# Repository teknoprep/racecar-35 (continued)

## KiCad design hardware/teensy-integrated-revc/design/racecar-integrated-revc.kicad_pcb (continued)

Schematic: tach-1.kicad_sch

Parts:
C19: 1n; C_0805_2012Metric
C20, C21: 100n; C_0805_2012Metric
D4: LM4040 2.5; SOT-23
D5: PMEG2010ER; Nexperia_CFP3_SOD-123W
J3: TACH INPUT; TerminalBlock_Phoenix_MKDS-1,5-2-5.08_1x02_P5.08mm_Horizont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
Q1: MMBT3904; SOT-23
R4: 180k 1%; R_0805_2012Metric
R5: 22k 1%; R_0805_2012Metric
R6: 240k 1%; R_0805_2012Metric
R7, R10: 10k 1%; R_0805_2012Metric
R8: 2.2M 1%; R_0805_2012Metric
R9: 4.7k 1%; R_0805_2012Metric
R11: 100k 1%; R_0805_2012Metric
U11: LM2903B; SOIC-8_3.9x4.9mm_P1.27mm

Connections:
+5V_MAIN: C21.1, R6.1, R9.1, U11.8 (VCC); also elsewhere on the board
GND: C19.2, C20.2, C21.2, D4.2 (A), D4.3 (A/NC), D5.2 (A), J3.2 (RETURN), Q1.2 (E), R5.2, R7.2, R11.2, U11.4 (GND), U11.5 (IN2+); also elsewhere on the board
TACH_BASE: Q1.1 (B), R10.2, R11.1
TACH_CMP: R8.1, R9.2, R10.1, U11.1 (OUT1)
TACH_IN: J3.1 (SIGNAL), R4.1
TACH_LED_K: Q1.3 (C); also elsewhere on the board
TACH_REF: C20.1, R6.2, R7.1, U11.2 (IN1-), U11.6 (IN2-)
TACH_SENSE: C19.1, D4.1 (K), D5.1 (K), R4.2, R5.1, R8.2, U11.3 (IN1+)

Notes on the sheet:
REV C / TACH-1
Prototype circuit; manufacturer pin names/MPNs recorded in components.json and BOM.csv.
Supply grounds shared. Analog shunts precede powered-off isolation. New oil/NTC conversion and WiFi firmware required.
NEVER coil/injector tach; NEVER screen 3V3_OUT as power input. Cut Teensy VUSB-VIN. CR2032 is not rechargeable.

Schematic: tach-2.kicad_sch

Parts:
C22: 100n; C_0805_2012Metric
R12: 680 1%; R_0805_2012Metric
R13: 4.7k 1%; R_0805_2012Metric
U12: VO617A-3; SMDIP-4_W9.53mm
U13: SN74LVC2G17; SOT-23-6

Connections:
+3V3_MCU: C22.1, R13.1, U13.5 (VCC); also elsewhere on the board
+5V_MAIN: R12.1; also elsewhere on the board
GND: C22.2, U12.3 (E), U13.2 (GND); also elsewhere on the board
GPS_RX_MCU: U13.4 (2Y); also elsewhere on the board
GPS_TX_AUX: U13.3 (2A); also elsewhere on the board
TACH_LED_A: R12.2, U12.1 (LED A)
TACH_LED_K: U12.2 (LED K); also elsewhere on the board
TACH_MCU: U13.6 (1Y); also elsewhere on the board
TACH_OPTO: R13.2, U12.4 (C), U13.1 (1A)

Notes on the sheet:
REV C / TACH-2
Prototype circuit; manufacturer pin names/MPNs recorded in components.json and BOM.csv.
Supply grounds shared. Analog shunts precede powered-off isolation. New oil/NTC conversion and WiFi firmware required.
NEVER coil/injector tach; NEVER screen 3V3_OUT as power input. Cut Teensy VUSB-VIN. CR2032 is not rechargeable.

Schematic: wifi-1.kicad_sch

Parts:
C32: 10u; C_0805_2012Metric
C33, C35: 100n; C_0805_2012Metric
C34: 1u; C_0805_2012Metric
Q2: MMBT3904; SOT-23
R29, R30, R31, R36: 10k 1%; R_0805_2012Metric
R32: 100k 1%; R_0805_2012Metric
R33, R34, R35: 33 1%; R_0805_2012Metric
R37: 47k 1%; R_0805_2012Metric
U17: SN74LVC125A; TSSOP-14_4.4x5mm_P0.65mm
U18: SN74LVC2G125; VSSOP-8_2.3x2mm_P0.5mm

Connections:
+3V3_MCU: R36.1, U18.8 (VCC); also elsewhere on the board
+3V3_NET: C32.1, C33.1, C35.1, R29.1, R30.1, U17.13 (4OE_N), U17.14 (VCC); also elsewhere on the board
GND: C32.2, C33.2, C34.2, C35.2, Q2.2 (E), R32.2, R37.2, U17.1 (1OE_N), U17.4 (2OE_N), U17.7 (GND), U17.10 (3OE_N), U17.12 (4A), U18.1 (1OE_N), U18.4 (GND), U18.7 (2OE_N); also elsewhere on the board
NET_BOOT: R30.2; also elsewhere on the board
NET_CS: R33.2; also elsewhere on the board
NET_CS_MCU: R36.2, U17.2 (1A); also elsewhere on the board
NET_CS_PRE: R33.1, U17.3 (1Y)
NET_EN: C34.1, Q2.3 (C), R29.2; also elsewhere on the board
NET_IRQ: U18.6 (2A); also elsewhere on the board
NET_IRQ_MCU: U18.5 (2Y); also elsewhere on the board
NET_MISO: U18.2 (1A); also elsewhere on the board
NET_MISO_MCU: U18.3 (1Y); also elsewhere on the board
NET_MOSI: R34.2; also elsewhere on the board
NET_MOSI_MCU: U17.5 (2A); also elsewhere on the board
NET_MOSI_PRE: R34.1, U17.6 (2Y)
NET_RESET_ASSERT: R31.1; also elsewhere on the board
NET_RESET_BASE: Q2.1 (B), R31.2, R32.1
NET_SCK: R35.2; also elsewhere on the board
NET_SCK_MCU: R37.1, U17.9 (3A); also elsewhere on the board
NET_SCK_PRE: R35.1, U17.8 (3Y)

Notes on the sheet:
REV C / WIFI-1
Prototype circuit; manufacturer pin names/MPNs recorded in components.json and BOM.csv.
Supply grounds shared. Analog shunts precede powered-off isolation. New oil/NTC conversion and WiFi firmware required.
NEVER coil/injector tach; NEVER screen 3V3_OUT as power input. Cut Teensy VUSB-VIN. CR2032 is not rechargeable.

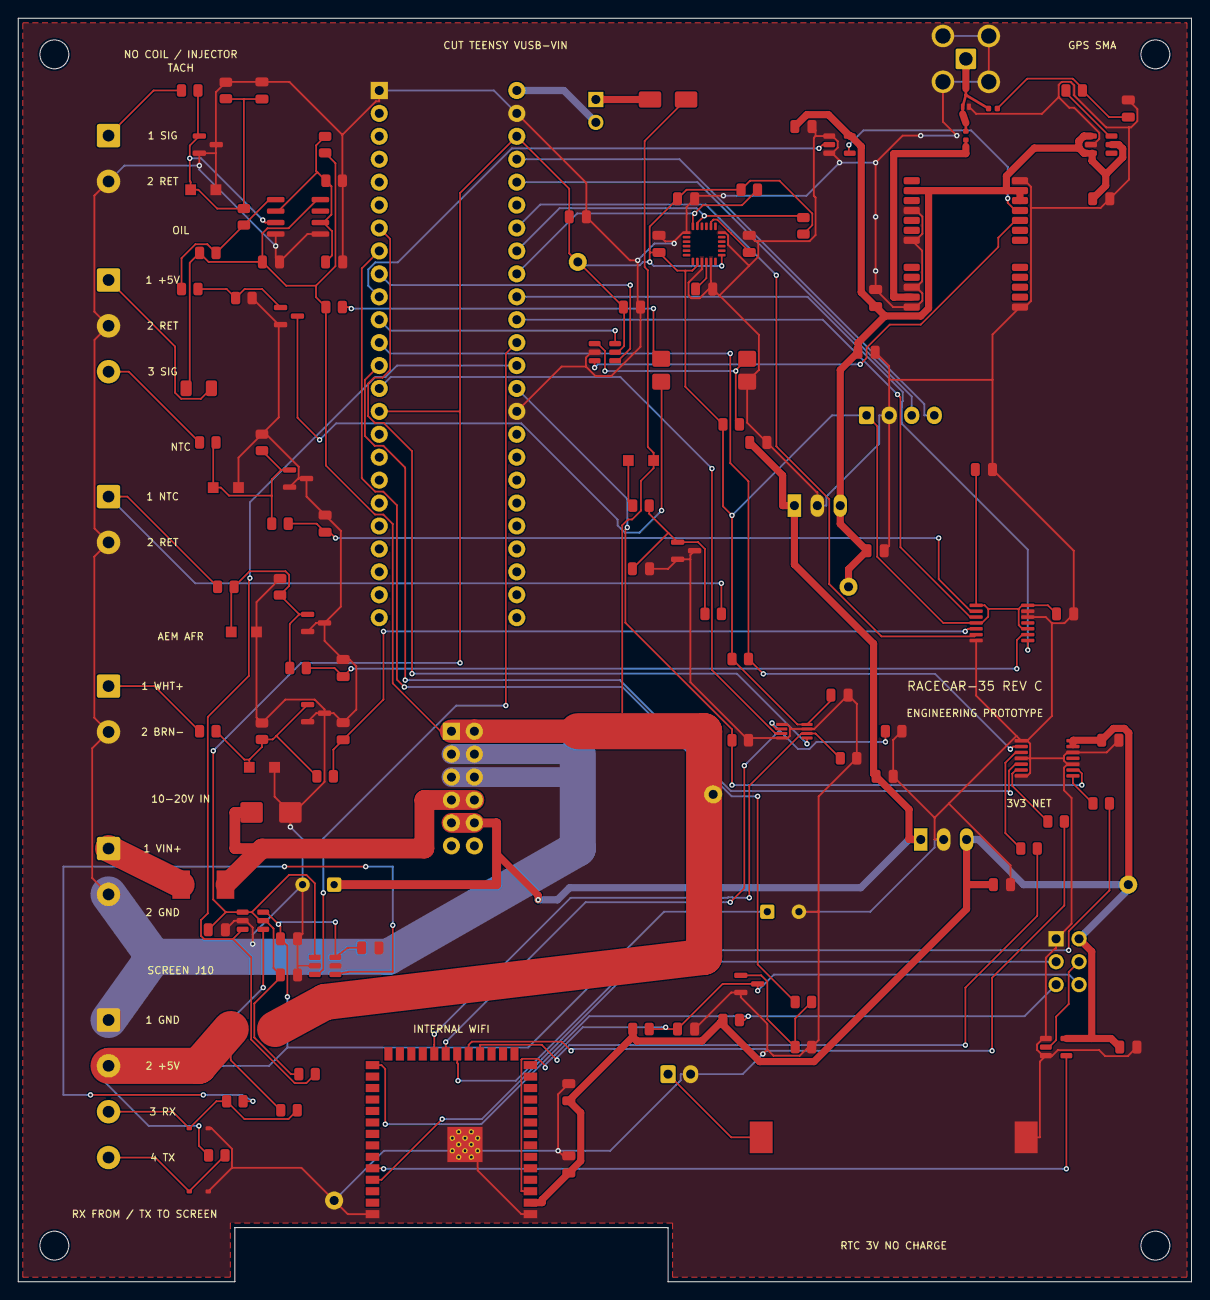
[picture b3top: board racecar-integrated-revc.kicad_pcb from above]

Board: 2 copper layers, 130.0 x 140.0 mm, 136 parts (0 on the bottom side), 76 nets.

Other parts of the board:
C36, C37: 100n; C_0805_2012Metric
J10: NET 3V3 UART SERVICE; PinHeader_2x03_P2.54mm_Vertical
R38, R39: 47k 1%; R_0805_2012Metric
U16: ESP32-S3-WROOM-1-N8R2; ESP32-S3-WROOM-1
U19: SN74LVC1G125; SOT-23-5

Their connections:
+3V3_MCU: C36.1; also elsewhere on the board
+3V3_NET: C37.1, J10.2, U16.2, U19.5; also elsewhere on the board
GND: C36.2, C37.2, J10.1, R38.2, R39.2, U16.1, U16.40, U16.41, U19.1, U19.3; also elsewhere on the board
NET_BOOT: J10.5, U16.27; also elsewhere on the board
NET_CS: U16.18; also elsewhere on the board
NET_EN: J10.6, U16.3; also elsewhere on the board
NET_IRQ: R38.1, U16.22; also elsewhere on the board
NET_MISO: R39.1, U16.21; also elsewhere on the board
NET_MOSI: U16.19; also elsewhere on the board
NET_SCK: U16.20; also elsewhere on the board
NET_UART_EXT_RX: J10.4, U19.2
NET_UART_RX: U16.36, U19.4
NET_UART_TX: J10.3, U16.37

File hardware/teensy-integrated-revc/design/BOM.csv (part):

Reference,Function,Value,Manufacturer,MPN,Footprint,Notes
U2,U2,Pololu D36V50F5,Pololu,4091 / D36V50F5,RacecarC:Pololu_D36V50F5,2x6 header; raised module; both output/ground columns fitted. EN/PG unused.
U3,U3,TSR 1-2433,TRACO Power,TSR 1-2433,RacecarC:Converter_DCDC_TRACO_TSR-1_THT,"Separate 1A module fed by Pololu VRP (10-20V protected), NOT marginal 5V input."
C3,C_U3I,100n,Murata,GRM21BR71H104KA01L,RacecarC:C_0805_2012Metric,X7R 50V; 10uF is X5R 25V
C4,C_U3O,10u,Murata,GRM21BR61E106KA73L,RacecarC:C_0805_2012Metric,X7R 50V; 10uF is X5R 25V
U6,U_NET_PWR,TSR 1-2433,TRACO Power,TSR 1-2433,RacecarC:Converter_DCDC_TRACO_TSR-1_THT,"Separate 1A module fed by Pololu VRP (10-20V protected), NOT marginal 5V input."
C5,C_U_NET_PWRI,100n,Murata,GRM21BR71H104KA01L,RacecarC:C_0805_2012Metric,X7R 50V; 10uF is X5R 25V
C6,C_U_NET_PWRO,10u,Murata,GRM21BR61E106KA73L,RacecarC:C_0805_2012Metric,X7R 50V; 10uF is X5R 25V
J1,J1,POWER IN,Phoenix Contact,1729018,"RacecarC:TerminalBlock_Phoenix_MKDS-1,5-2-5.08_1x02_P5.08mm_Horizontal",
F1,F1,5A fuse,Littelfuse,0451005.MRL,RacecarC:Fuse_Littelfuse-NANO2-451_453,
F2,F2,4A fuse,Littelfuse,0451004.MRL,RacecarC:Fuse_Littelfuse-NANO2-451_453,
D1,D1,SMBJ20CA,Littelfuse,SMBJ20CA,RacecarC:D_SMB,Bidirectional TVS; NOT automotive load-dump qualification
C1,C1,100uF 50V,Panasonic,EEU-FR1H101,RacecarC:CP_Radial_D8.0mm_P3.50mm,
C2,C2,470uF 10V,Panasonic,EEU-FR1A471B,RacecarC:CP_Radial_D8.0mm_P3.50mm,
D2,D2,SS14,Diodes Incorporated,SS14,RacecarC:D_SMA,
JP1,JP1,MCU POWER,Samtec,TSW-102-07-G-S,RacecarC:PinHeader_1x02_P2.54mm_Vertical,Fit shunt after unloaded rail tests; cut Teensy VUSB-VIN before dual-power use
U1,U1,Teensy 4.1 SOCKETED,PJRC,TEENSY41,RacecarC:Teensy41_Socket,CUT VUSB-VIN. Two 24-pin sockets. VBAT via separate removable 2-wire service lead to labelled Teensy VBAT/GND pads.
C7,C_MCU,100n,Murata,GRM21BR71H104KA01L,RacecarC:C_0805_2012Metric,X7R 50V; 10uF is X5R 25V
BT1,BT1,CR2032 HOLDER,Keystone,1058,RacecarC:BatteryHolder_Keystone_1058_1x2032,Fit Panasonic CR2032 AFTER reflow/cleaning. Primary cell: NO charging.
J9,J_BAT,TO TEENSY VBAT/GND,JST,B2B-XH-A(LF)(SN),RacecarC:JST_XH_B2B-XH-A_1x02_P2.50mm_Vertical,"Short removable lead: 1 to Teensy VBAT auxiliary pad, 2 GND. NEVER 3V3/ONOFF. Required assembly operation."
J7,J6,CAN MODULE LOGIC,JST,B4B-XH-A(LF)(SN),RacecarC:JST_XH_B4B-XH-A_1x04_P2.50mm_Vertical,"External SN65HVD230 module only, powered from this header. Not CANH/L. No independent module power."
C8,C_CAN,100n,Murata,GRM21BR71H104KA01L,RacecarC:C_0805_2012Metric,X7R 50V; 10uF is X5R 25V
U7,U_IMU,MPU-6050,TDK InvenSense,MPU-6050,RacecarC:InvenSense_QFN-24_4x4mm_P0.5mm,Legacy part matched to firmware. Authorized genuine stock required; NO unreviewed substitute. Lifecycle/procurement gate before order.
C9,C_IMUV,100n,Murata,GRM21BR71H104KA01L,RacecarC:C_0805_2012Metric,X7R 50V; 10uF is X5R 25V
C10,C_IMUL,10n,Murata,GRM21BR71H103KA01L,RacecarC:C_0805_2012Metric,X7R 50V; 10uF is X5R 25V
C11,C_IMUR,100n,Murata,GRM21BR71H104KA01L,RacecarC:C_0805_2012Metric,X7R 50V; 10uF is X5R 25V
C12,C_IMUP,2.2n,Murata,GRM21BR71H222KA01L,RacecarC:C_0805_2012Metric,X7R 50V; 10uF is X5R 25V
R1,R_SDA,4.7k 1%,Yageo,RC0805FR-074K7L,RacecarC:R_0805_2012Metric,0805; >=0.125W
R2,R_SCL,4.7k 1%,Yageo,RC0805FR-074K7L,RacecarC:R_0805_2012Metric,0805; >=0.125W
U8,U_GPS,NEO-M9N-00B,u-blox,NEO-M9N-00B,RacecarC:ublox_NEO,"USB disabled: V_USB GND, D+/- open. No GPS coin-cell load: V_BCKP=VCC. VCC_RF unused; antenna bias from protected AUX rail."
C13,C_GPS1,100n,Murata,GRM21BR71H104KA01L,RacecarC:C_0805_2012Metric,X7R 50V; 10uF is X5R 25V
C14,C_GPS2,10u,Murata,GRM21BR61E106KA73L,RacecarC:C_0805_2012Metric,X7R 50V; 10uF is X5R 25V
J8,J_ANT,GPS SMA FEMALE,Amphenol RF,901-143,RacecarC:SMA_Amphenol_901-143_Horizontal,"Active GPS antenna 3.3V bias, never WiFi. Supplier drawing/board-edge fit must be inspected."
C15,C_RF,100pF C0G,Murata,GRM1555C1H101JA01D,RacecarC:C_0402_1005Metric,
L1,L_RF,27nH RF choke,Murata,LQG15HS27NJ02D,RacecarC:L_0402_1005Metric,
D3,D_RF,RF ESD,Nexperia,"PESD3V3U1UL,315",RacecarC:D_SOD-882,RF-rated low-capacitance ESD. Verify capacitance/S-parameter budget at GNSS bands.
U9,U_ANT,TPS2553,Texas Instruments,TPS2553DBVR,RacecarC:SOT-23-6,"ILIM tied to IN: 50/75/100mA min/typ/max limit per datasheet. Antenna fed from AUX, not GPS VCC_RF."
R3,R_ANT_FILTER,10R 1%,Yageo,RC0805FR-0710RL,RacecarC:R_0805_2012Metric,
C16,C_ANT_IN,100n,Murata,GRM21BR71H104KA01L,RacecarC:C_0805_2012Metric,X7R 50V; 10uF is X5R 25V
C17,C_ANT_OUT,100n,Murata,GRM21BR71H104KA01L,RacecarC:C_0805_2012Metric,X7R 50V; 10uF is X5R 25V
U10,U_GTX,SN74LVC1G125,Texas Instruments,SN74LVC1G125DBVR,RacecarC:SOT-23-5,
C18,C_GTX,100n,Murata,GRM21BR71H104KA01L,RacecarC:C_0805_2012Metric,X7R 50V; 10uF is X5R 25V
J3,J_TACH,TACH INPUT,Phoenix Contact,1729018,"RacecarC:TerminalBlock_Phoenix_MKDS-1,5-2-5.08_1x02_P5.08mm_Horizontal",ECU/cluster conditioned 3.3/5/battery-level waveform ONLY. NEVER coil or injector.
R4,R_TTOP,180k 1%,Yageo,RC0805FR-07180KL,RacecarC:R_0805_2012Metric,0805; >=0.125W
R5,R_TBOT,22k 1%,Yageo,RC0805FR-0722KL,RacecarC:R_0805_2012Metric,0805; >=0.125W
C19,C_TFILTER,1n,Murata,GRM21BR71H102KA01L,RacecarC:C_0805_2012Metric,X7R 50V; 10uF is X5R 25V
D4,D_TPOS,LM4040 2.5,Texas Instruments,LM4040AIM3-2.5/NOPB,RacecarC:SOT-23,
D5,D_TNEG,PMEG2010ER,Nexperia,"PMEG2010ER,115",RacecarC:Nexperia_CFP3_SOD-123W,
U11,U_CMP,LM2903B,Texas Instruments,LM2903BIDR,RacecarC:SOIC-8_3.9x4.9mm_P1.27mm,
R6,R_TREFH,240k 1%,Yageo,RC0805FR-07240KL,RacecarC:R_0805_2012Metric,0805; >=0.125W
R7,R_TREFL,10k 1%,Yageo,RC0805FR-0710KL,RacecarC:R_0805_2012Metric,0805; >=0.125W
C20,C_TREF,100n,Murata,GRM21BR71H104KA01L,RacecarC:C_0805_2012Metric,X7R 50V; 10uF is X5R 25V
C21,C_CMP,100n,Murata,GRM21BR71H104KA01L,RacecarC:C_0805_2012Metric,X7R 50V; 10uF is X5R 25V
R8,R_THYST,2.2M 1%,Yageo,RC0805FR-072M2L,RacecarC:R_0805_2012Metric,0805; >=0.125W
R9,R_TPULL,4.7k 1%,Yageo,RC0805FR-074K7L,RacecarC:R_0805_2012Metric,0805; >=0.125W
R10,R_TBASE,10k 1%,Yageo,RC0805FR-0710KL,RacecarC:R_0805_2012Metric,0805; >=0.125W
R11,R_TBE,100k 1%,Yageo,RC0805FR-07100KL,RacecarC:R_0805_2012Metric,0805; >=0.125W
Q1,Q_TLED,MMBT3904,Nexperia,"MMBT3904,215",RacecarC:SOT-23,
R12,R_TLED,680 1%,Yageo,RC0805FR-07680RL,RacecarC:R_0805_2012Metric,0805; >=0.125W
U12,U_OPTO,VO617A-3,Vishay,VO617A-3X017T,RacecarC:SMDIP-4_W9.53mm,"100-200% CTR grade; ground shared, not whole-system galvanic isolation."
R13,R_TOPULL,4.7k 1%,Yageo,RC0805FR-074K7L,RacecarC:R_0805_2012Metric,0805; >=0.125W
U13,U_INPUT,SN74LVC2G17,Texas Instruments,SN74LVC2G17DBVR,RacecarC:SOT-23-6,"Inputs tolerate 5.5V, Ioff isolation; GPS AUX cannot back-power MCU through this buffer."
C22,C_INPUT,100n,Murata,GRM21BR71H104KA01L,RacecarC:C_0805_2012Metric,X7R 50V; 10uF is X5R 25V
J4,J_OIL,OIL 0.5-4.5V,Phoenix Contact,1729021,"RacecarC:TerminalBlock_Phoenix_MKDS-1,5-3-5.08_1x03_P5.08mm_Horizontal",
F3,F_SENSOR,100mA PTC,Littelfuse,1206L010/30YR,RacecarC:Fuse_1206_3216Metric,
J5,J_COOL,COOLANT NTC,Phoenix Contact,1729018,"RacecarC:TerminalBlock_Phoenix_MKDS-1,5-2-5.08_1x02_P5.08mm_Horizontal",
J6,J_AFR,AEM 30-0300 ONLY,Phoenix Contact,1729018,"RacecarC:TerminalBlock_Phoenix_MKDS-1,5-2-5.08_1x02_P5.08mm_Horizontal",External AEM gauge only. Gauge supply/heater NOT powered here.
R14,R_OILH,20k 0.1%,Yageo,RT0805BRD0720KL,RacecarC:R_0805_2012Metric,Thin-film 0.1%
R15,R_OILL,20k 0.1%,Yageo,RT0805BRD0720KL,RacecarC:R_0805_2012Metric,Thin-film 0.1%
D6,D_OILP,LM4040 3.0,Texas Instruments,LM4040AIM3-3.0/NOPB,RacecarC:SOT-23,
D7,D_OILN,PMEG2010ER,Nexperia,"PMEG2010ER,115",RacecarC:Nexperia_CFP3_SOD-123W,
R16,R_OILF,1k 1%,Yageo,RC0805FR-071KL,RacecarC:R_0805_2012Metric,0805; >=0.125W
C23,C_OILF,100n,Murata,GRM21BR71H104KA01L,RacecarC:C_0805_2012Metric,X7R 50V; 10uF is X5R 25V
R17,R_AFRH,20k 0.1%,Yageo,RT0805BRD0720KL,RacecarC:R_0805_2012Metric,Thin-film 0.1%
R18,R_AFRL,20k 0.1%,Yageo,RT0805BRD0720KL,RacecarC:R_0805_2012Metric,Thin-film 0.1%
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
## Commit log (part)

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2026-05-16 Sync working state: dash UI, Teensy main, setup docs
    - RaceDash.ino: latest dash UI work (track picker, settings, anti-flicker)
    - src/main.cpp: latest Teensy GNSS + tach + dash protocol
    - Add SETUP.md
    - .vscode tweaks and minor README/baseline updates
2026-05-16 Dash keyboard: swap '/' for '@' so emails are typeable
    Cloud host is always a bare DNS name (no paths) and emails universally
    need '@', so '/' was dead weight on the text keyboard. Bottom-right key
    on row 4 now types '@'.
2026-05-16 Phase 1: Internet mode (Ethernet/WiFi) + FIRMWARE_VERSION + dash WiFi NTP
    CrowPanel (RaceDash.ino):
    - New SettingId rows at top of settings: ST_INET_MODE, ST_WIFI_SSID,
    ST_WIFI_PASS, ST_WIFI_STATUS (last 3 hidden when mode=Ethernet).
    - New SettingRow::INFO kind for read-only display rows (WiFi status).
    - INET_MODE_NAMES = { 'Ethernet', 'WiFi' }; default 0 (Ethernet).
    - Settings struct: internet_mode (uint8), wifi_ssid[33], wifi_pass[64].
2026-05-16 Upload progress modal + cancel-until-reboot
    While the Teensy is uploading a file (after-race POST or queue drain),
    the dash now pops a full-screen blocking modal:
    +---------------------------------------------------+
    | |
    | +-----------------------------------------+ |
    | | Uploading session | |
2026-05-16 Release v0.1.1 \u2014 first OTA test target
    Trivial content change for the upgrade-flow test: the PAGE_TOOLS footer
    now also stamps the running firmware version so it's obvious whether
    the OTA actually landed:
    before: 'swipe right <- to return to STATUS'
    after: 'firmware v0.1.1 - swipe right <- STATUS'
    After push, a dash running v0.1.0 -> tap 'Check for updates' on TOOLS
2026-05-16 STATUS: show dash + teensy firmware versions with mismatch button
    - Teensy emits 'VER,teensy,<version>' at boot AND in reply to 'VER?'.
    - Dash sends 'VER?' on its own boot and whenever the STATUS page opens
    so the value can't be silently stale from a missed boot announcement.
    - New FIRMWARE section bottom-left of STATUS:
    DASH v0.1.4
    TEENSY v0.1.0 (in dark-grey '...' if not received yet)
2026-05-16 Phase 2b fix: 32KB Teensy UART RX buffer + better FlasherX diagnostics
    Root cause of the v0.1.6 -> v0.1.7 Teensy OTA failure:
    - Teensy DASH_SERIAL RX buffer was 2 KB (~22 ms of slack at 921 600 baud)
    - FlasherX flash_write_block() does a 4 KB sector erase whenever the staged
    image crosses a sector boundary, stalling the read loop ~25-100 ms
    - At 921 600 baud, 25-100 ms = 2.3-9.2 KB streaming in while we can't read
    - 2 KB buffer overflows, losing chars MID-LINE on whatever record happens
2026-05-16 Release v0.1.11: quiet CrowPanel OTA flash path
    The dash update path was still writing flash directly from the HTTPS stream
    while also repainting the OTA modal. During Update.write() flash erases/writes,
    the RGB panel scan-out could catch intermediate draw states and produce hard
    screen flashing.
    Fix CrowPanel self-update path to mirror the Teensy-hex path:
    - Download full crowpanel-dash.bin into PSRAM first.
2026-05-16 Release v0.1.15: avoid stale Teensy version and don't block after commit
    Field testing showed two distinct OTA verifier problems:
    1. After a false Teensy failure, retrying did not go directly to the dash
    update. The dash still had a stale cached Teensy version, so it believed
    the Teensy needed flashing again until a later VER line refreshed state.
    2. Once FlasherX has accepted the image and emitted FW,COMMITTING, failing
    the entire combined update solely because the dash missed a later VER line
2026-05-16 Release v0.1.18: add direct Teensy USB FlasherX test path
    Add a developer-only Teensy USB CDC firmware update path to decouple FlasherX
    validation from the CrowPanel/GitHub/WiFi/UART bridge.
    New Teensy USB command:
    USBFWUPDATE
    It enters the same per-line ACK FlasherX path used by dash OTA, but over the
    Teensy's native USB Serial stream. This allows local tests using a freshly
2026-05-16 Release v0.1.22: WiFi-via-dash cloud uploads, HTTPS default, test mode
    Phase 3 / cloud upload routing:
    - New UART protocol 'WUP,*' for forwarding NDJSON session files from Teensy to
    Dash over UART. Dash buffers in PSRAM, then HTTPS-POSTs to /upload on the
    configured cloud endpoint using the same headers the Ethernet path uses
    (X-API-Key, X-User-Email, X-Session-Id, X-Track-Name).
    - Per-line 'U' ACK protocol keeps UART throughput safe across PSRAM appends.
2026-05-16 Release v0.1.25: cap dash page redraw to 25 Hz to reduce screen tearing
    At 25 Hz Teensy telemetry, the dash was repainting the big dynamic elements
    (speed digit, RPM bar, ENG/GPS strings) up to twice per fresh telemetry frame
    because the dash redraw was running at 50 Hz. Any repaint that landed
    mid-LCD-scan produced a visible tear on those large screen areas.
    Drop the PAGE_DASH redraw cadence from 20 ms (50 Hz) to 40 ms (25 Hz) so each
    fresh sample is rendered exactly once. This doesn't eliminate tearing
2026-05-16 Release v0.1.29: manual UPLOAD button + immediate queue drain
    Add a dash-page UPLOAD button so the user can trigger queued-session
    upload immediately instead of waiting for the next 10 s cloudTick walker.
    Dash side:
    - New button at (210, 155, 180, 70), between START and the speed digit.
    - Visible only when (!recording) && (cloud_queue_depth > 0).
    - Tap sends 'QUEUE,DRAIN' over UART.
2026-05-16 Release v0.1.32: more aggressive SD detect + visible error code on dash
    User reports: SD card shows 'No Card' after reboot even though card is
    physically present and was working before. Existing 4-attempt 50ms retry
    in v0.1.31 isn't enough for their card + slot combo.
    SD detection:
    - detectSD() retries bumped to 8 mount attempts + 4 raw-card probes with
    100 ms delays. Worst-case ~1.2 s budget per detect call.
2026-05-16 Release v0.1.36: surface server response body on upload failure
    User reports: larger session files (~1 MB) fail with 'FAIL: http 422'.
    The dash was throwing away the server's response body, which on FastAPI
    includes the actual reason (e.g. {'detail': [...]} validation errors).
    Fix: on any non-2xx HTTP response in ufDoPost(), call http.getString() to
    read the response body, strip newlines, and embed a snippet into the error
    message. The modal now shows e.g.:
2026-05-18 Release v0.1.39: fix Q,A flow-control + faster TCP path on cloud uploads
    - CrowPanel was never sending Q,A acks on the streaming upload path, so
    the Teensy hit Q,ERR,ack_timeout on the very first sample of every
    upload that used the dash-driven Q protocol. Send Q,A after each Q,L
    line is written to the cloud TCP socket so the Teensy is paced properly.
    - Bump UART line parser max from 256 to 512 bytes so long NDJSON samples
    wrapped as 'Q,L,<line>' aren't truncated mid-upload (Teensy line buffer
2026-06-01 server: production docker-compose with Caddy auto-HTTPS; Teensy SDLS diagnostic
    - server/docker-compose.prod.yml: app + Caddy reverse proxy with automatic
    Let's Encrypt TLS for RACECAR_DOMAIN (dash defaults to HTTPS). App stays on
    the internal docker network; only Caddy is exposed (80/443).
    - server/Caddyfile: auto-HTTPS, gzip, 96MB body limit, proxy to cloud:8089.
    - server/.env.example: add RACECAR_DOMAIN + ACME_EMAIL; HTTPS redirect URI.
    - src/main.cpp: add USB 'SDLS' command to list /sessions, /queue, /cansniff
2026-06-02 server: add admin portal for managing authorized Gmail accounts
    - New /admin page (admins only): add/remove authorized accounts and
    grant/revoke admin, persisted to /data/users.json (no redeploy needed).
    - RACECAR_ADMIN_EMAILS bootstraps the first admin(s); setting it activates
    the sign-in allowlist (union of env admins + env allowed + managed users).
    - Admin link surfaces in the header for admin accounts.
    - Wire RACECAR_ADMIN_EMAILS into both compose files + .env.example/README.
2026-06-03 Add lap timing: cloud lap detection + delta, dash best-lap delta
    Server:
    - /sessions/<user>/<file>/laps endpoint auto-detects start/finish from the
    GPS trace (no track table) and returns per-lap times + fastest lap
    - Review page: lap table (best highlighted), click-to-select a lap with
    best-lap ghost overlay on the map, and a distance-aligned delta-vs-best trace
    Dash (RaceDash.ino):
2026-06-03 Admin: upload + review CAN sniffer captures in the browser
    New admin-only CAN-bus portal (/admin/canbus):
    - Upload a CAN sniffer CSV (t_ms,id,ext,dlc,d0..d7) via a plain file picker
    (raw POST body, no python-multipart dep); stored under data/canbus/
    - Review page parses server-side and shows per-ID frame counts + rates and
    per-byte min/max/range, with a bytes-over-time plot (changing bytes on by
    default) and a 16-bit word inspector (start byte + BE/LE) to pinpoint which
2026-06-03 Release v0.1.42: bump CrowPanel to match Teensy (no version mismatch)
    Previous commit shipped Teensy 0.1.42 but left CrowPanel at 0.1.41 -> field
    version mismatch. Bump CrowPanel FIRMWARE_VERSION to 0.1.42, rebuild
    crowpanel-dash.bin, update manifest (crowpanel version + sha256). Now both
    MCUs release at the same version.
    Also document the OTA release procedure + lockstep-version rule in CLAUDE.md.
    crowpanel sha256 8d8043fea1d31a0fb46b003e4fc83fb61a177f0300f7f672d847bacd00e85b51
2026-06-03 Release v0.1.45: CANDIAG now reports dup% + FlexCAN ACK/CRC/error-counter/bus state. Diagnosed running-engine capture: 0x5E8 byte-identical to engine-off frame at ~3600fps = ACK-error retransmit stor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
2026-06-03 Release v0.1.49: run Teensy CAN in LISTEN-ONLY mode (CTRL1.LOM). Dash is a pure consumer; listen-only never transmits/ACKs/errors so it can NEVER go bus-off - eliminates the 'first packets work then 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
2026-06-03 Release v0.1.52: plain-English CAN verdict on dash. Uses Teensy RX error counter to say WHO is at fault: storm+RXe high = our ACK not reaching bus (TX path); storm+RXe~0 = MS3-side. No more reading r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
2026-06-04 Release v0.1.56: fix Direct-mode RPM (was on pin 22 via plain FreqMeasure) + add Tach pulses/rev divider
    - Direct-mode tach never worked: plain FreqMeasure is hard-wired to pin 22
    (FlexPWM4 CH0-A = CAN1 TX) on Teensy 4.x and ignored pin 9. Switched to
    FreqMeasureMulti.begin(9) (FlexPWM2_2_B), verified capturing real edges.
    - New setting 'Tach pulses/rev' (Settings, ENUM 0.5/1/2/3/4/6/8) = the
    Direct-mode RPM divider. Stored NVS 'rpmppr' x10, synced to Teensy via
    CFG,rpmppr,<x10>; Teensy divides opto-tach frequency by rpmppr/10.
2026-06-04 Release v0.1.59: RPM EMA off (alpha 1.0) - max snappy, median-of-3 still rejects spikes
2026-06-24 0.1.63: tach pulses/rev is now -/+ steppers (discrete 0.5..8 list)
2026-06-29 Release v0.1.67: IMU boot auto-calibration (gyro bias + accel scale)
    - calibrateIMU(): every-boot gyro bias removal + accel scale-normalize to 1g,
    gated by a stillness check (rejects cal if moving, keeps last-good offsets).
    - Last-good offsets persisted to Teensy EEPROM (addr 0, magic 0xCA15).
    - readImuRaw(): buffer 14 bytes before int16 assembly (fixes byte-order UB).
    - Verified at rest: gyro ~0 dps, |a| = 1.00 g (was 26 dps / 1.41 g).
    - Docs: new CLAUDE.md IMU wiring + auto-cal section; EEPROM addr 0 reserved.
2026-06-30 RaceDash Mobile v0.1.2: in-app OTA self-update
    - UpdateManager: reads android/app-manifest.json from GitHub raw, compares
    versionCode with the installed APK, downloads the release APK (follows
    redirects, sha256-verified, progress), and launches the system installer via
    a FileProvider content URI. Honors the Android 8+ 'install unknown apps' gate
    (REQUEST_INSTALL_PACKAGES + ACTION_MANAGE_UNKNOWN_APP_SOURCES).
    - Auto-checks on launch (silent unless an update exists); manual 'Check for
